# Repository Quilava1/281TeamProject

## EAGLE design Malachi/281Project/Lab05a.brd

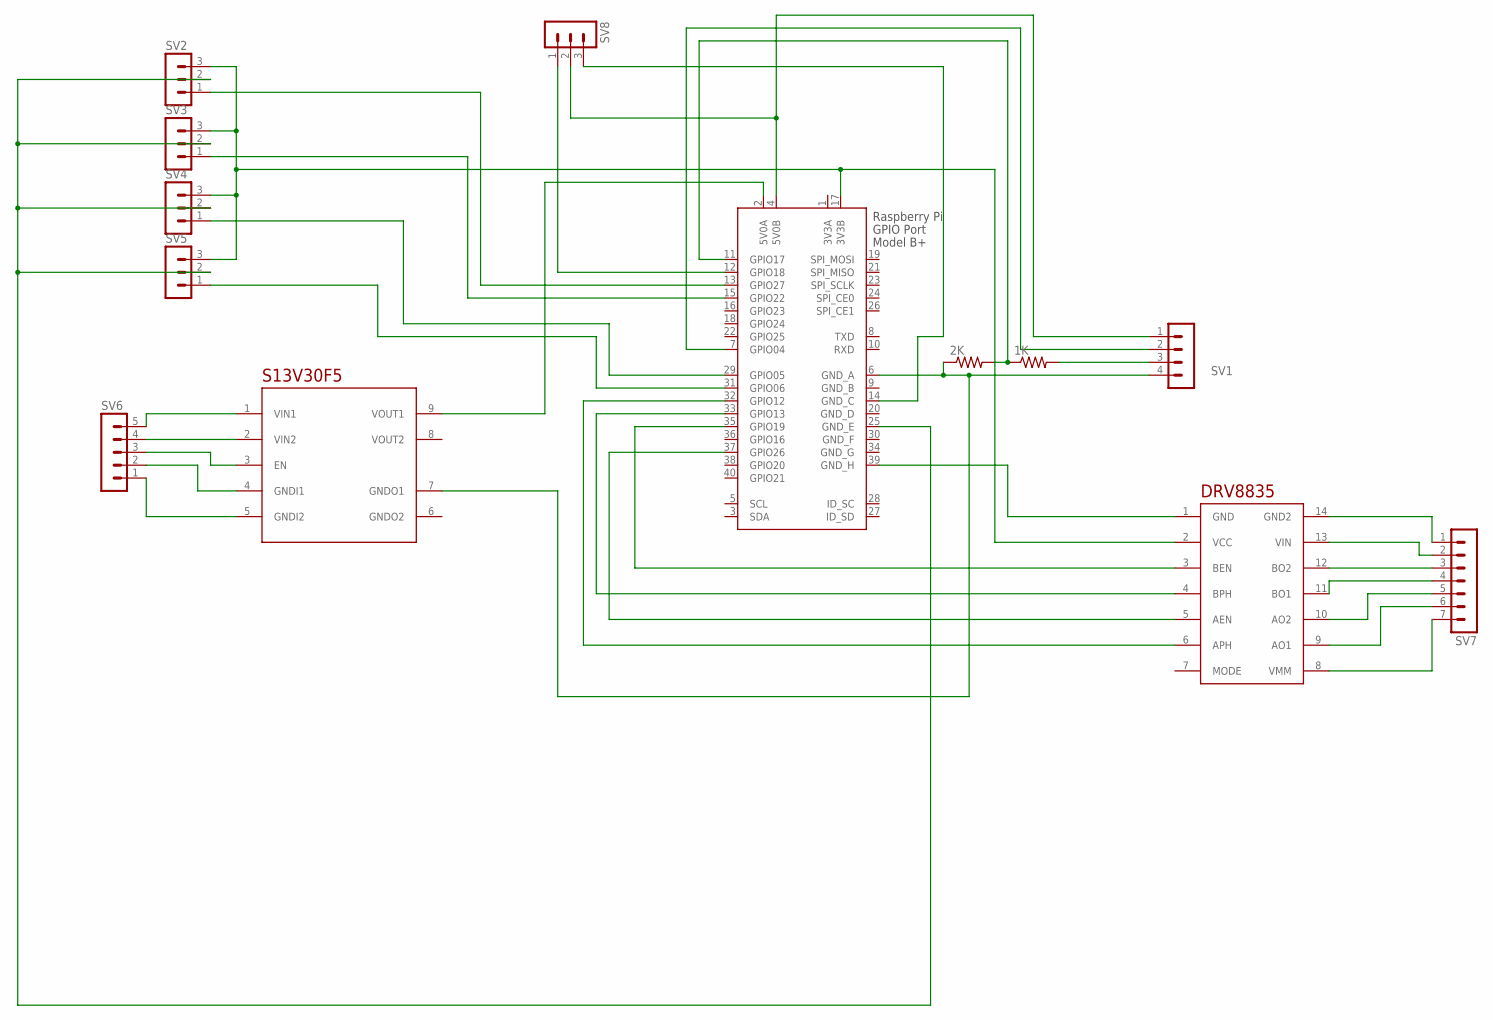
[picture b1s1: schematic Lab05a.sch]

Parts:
1K, 2K: R-US_0207/10; 0207/10
SV1: MA04-1
SV2, SV3, SV4, SV5, SV8: MA03-1
SV6: MA05-1
SV7: MA07-1
U$1: DRV8835
U$2: S13V20F5
X1: RASPI_BOARD_B+#_E4; RASPI_BOARD_B+_EDGES_4DRILL

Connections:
3V: SV2.3, SV3.3, SV4.3, SV5.3, U$1.2 (VCC), X1.17 (3V3B)
3V3A: X1.1 (3V3A)
GND: SV2.2, SV3.2, SV4.2, SV5.2, X1.25 (GND_E)
GND_B: X1.9 (GND_B)
GND_D: X1.20 (GND_D)
GND_F: X1.30 (GND_F)
GND_G: X1.34 (GND_G)
unnamed: SV1.1, SV8.2, X1.4 (5V0B)
unnamed: SV1.2, X1.7 (GPIO04)
unnamed: 1K.2, SV1.3
unnamed: 1K.1, 2K.2, X1.11 (GPIO17)
unnamed: 2K.1, SV1.4, U$2.7 (GNDO1), X1.6 (GND_A)
unnamed: SV7.1, U$1.14 (GND2)
unnamed: SV2.1, X1.13 (GPIO27)
unnamed: SV3.1, X1.15 (GPIO22)
unnamed: SV4.1, X1.29 (GPIO05)
unnamed: SV5.1, X1.31 (GPIO06)
unnamed: SV7.2, U$1.13 (VIN)
unnamed: U$1.4 (BPH), X1.33 (GPIO13)
unnamed: U$1.6 (APH), X1.32 (GPIO12)
unnamed: U$1.5 (AEN), X1.37 (GPIO26)
unnamed: U$1.3 (BEN), X1.35 (GPIO19)
unnamed: U$1.1 (GND), X1.39 (GND_H)
unnamed: U$2.9 (VOUT1), X1.2 (5V0A)
unnamed: SV7.3, U$1.12 (BO2)
unnamed: SV7.4, U$1.11 (BO1)
unnamed: SV7.5, U$1.10 (AO2)
unnamed: SV7.6, U$1.9 (AO1)
unnamed: SV7.7, U$1.8 (VMM)
unnamed: SV6.5, U$2.1 (VIN1)
unnamed: SV6.4, U$2.2 (VIN2)
unnamed: SV6.3, U$2.3 (EN)
unnamed: SV6.2, U$2.4 (GNDI1)
unnamed: SV6.1, U$2.5 (GNDI2)
unnamed: SV8.1, X1.12 (GPIO18)
unnamed: SV8.3, X1.14 (GND_C)

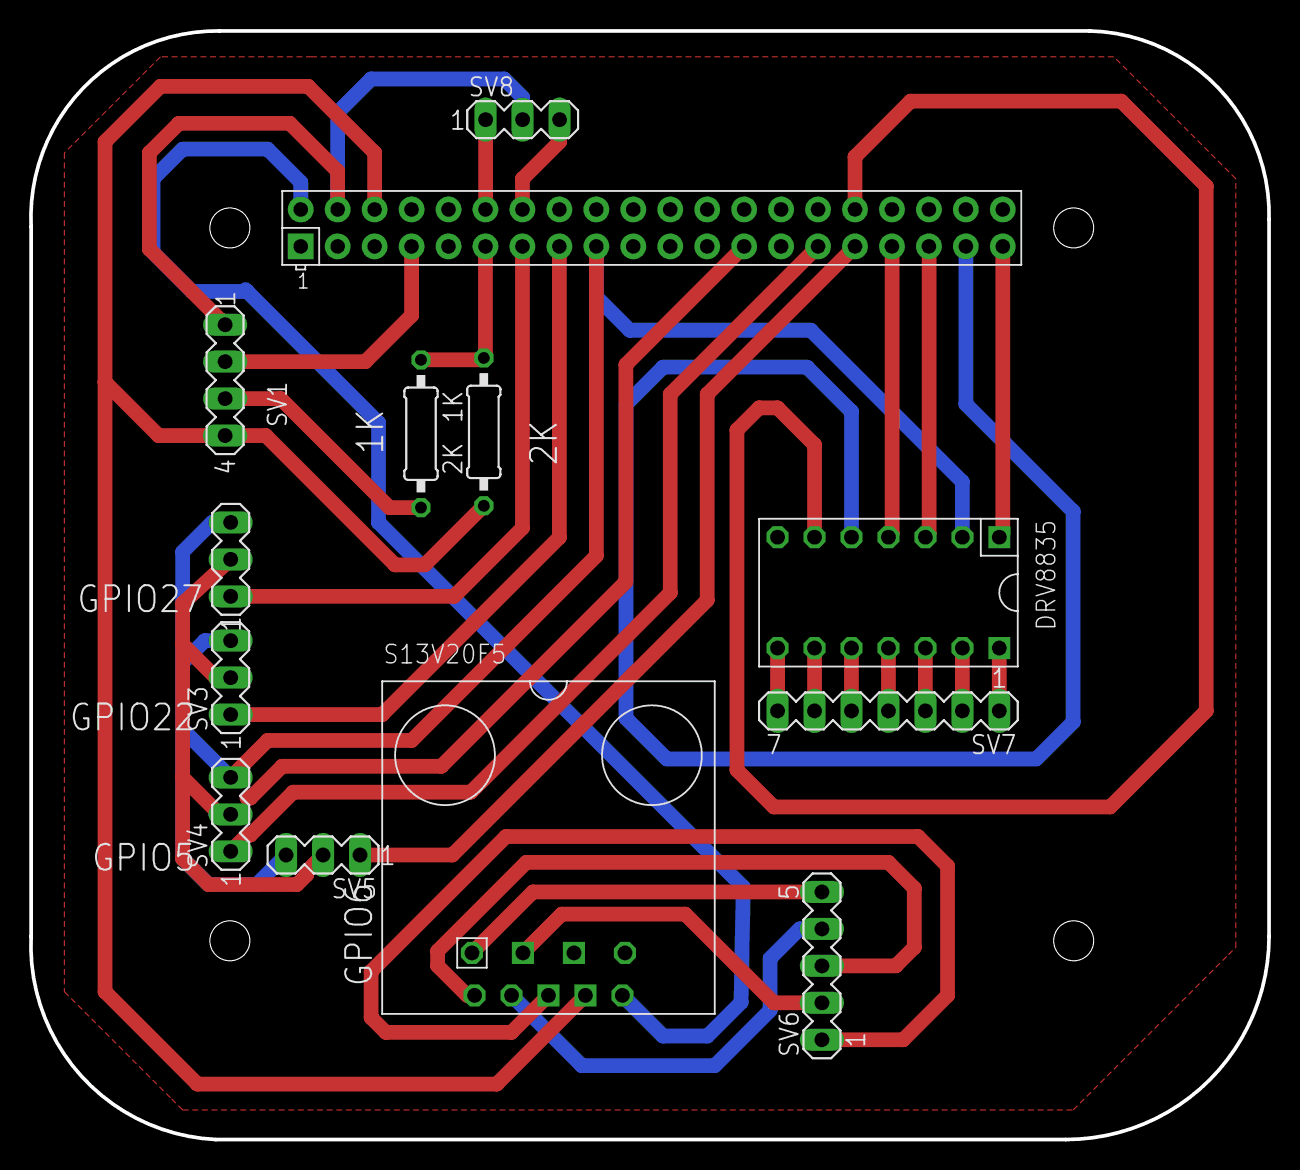
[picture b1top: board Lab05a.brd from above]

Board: 2 copper layers, 85.1 x 76.2 mm, 13 parts (0 on the bottom side), 31 nets.

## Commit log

2021-07-21 add Malachi
2021-07-21 add Gaith and Jack
2021-07-21 add Group
2021-07-22 baseplate uploaded
2021-07-23 attached wheel's for underneath mount design
2021-07-25 added cut dxf files
2021-07-25 updated cuts for steering and ultrasonic mount
2021-07-25 Offset the 4.75 cuts
2021-07-25 fixed 4.75 cuts
2021-07-25 offset 9mmCuts
2021-07-25 fixed offset for 4.75 mmCuts
2021-07-25 refixed offset for 4.75 mmCuts
2021-07-25 fixed 3mmCuts offsets
2021-07-25 Complete lasercut file
2021-07-25 fixed backbase hole alignment
2021-07-25 added steering assembly to cuts
2021-07-25 axle to cuts
2021-07-25 refixed backbase hole alignment
2021-07-25 updated cuts
2021-07-26 add new slot base
2021-07-26 readd new slot base
2021-07-26 rereadd new slot base
2021-07-26 updated cutfile with slot base design
2021-07-26 fixed cutfile slot base cut order
2021-07-26 moved the base edit part into the drawing folder
2021-07-26 hidden old base
2021-07-26 hidden base in cut
2021-07-29 added cadfiles zip file
2021-07-29 updated fix to include new steering system:
2021-07-29 fixed layers of the cut file
2021-07-30 added finalcut
2021-07-30 completed final cut
2021-08-08 add line follower
2021-08-15 added pcb
2021-08-15 finished pcb
2021-09-21 finishing line follower.py
2021-09-22 finished sensor lab
2021-09-22 completed sensor lab
